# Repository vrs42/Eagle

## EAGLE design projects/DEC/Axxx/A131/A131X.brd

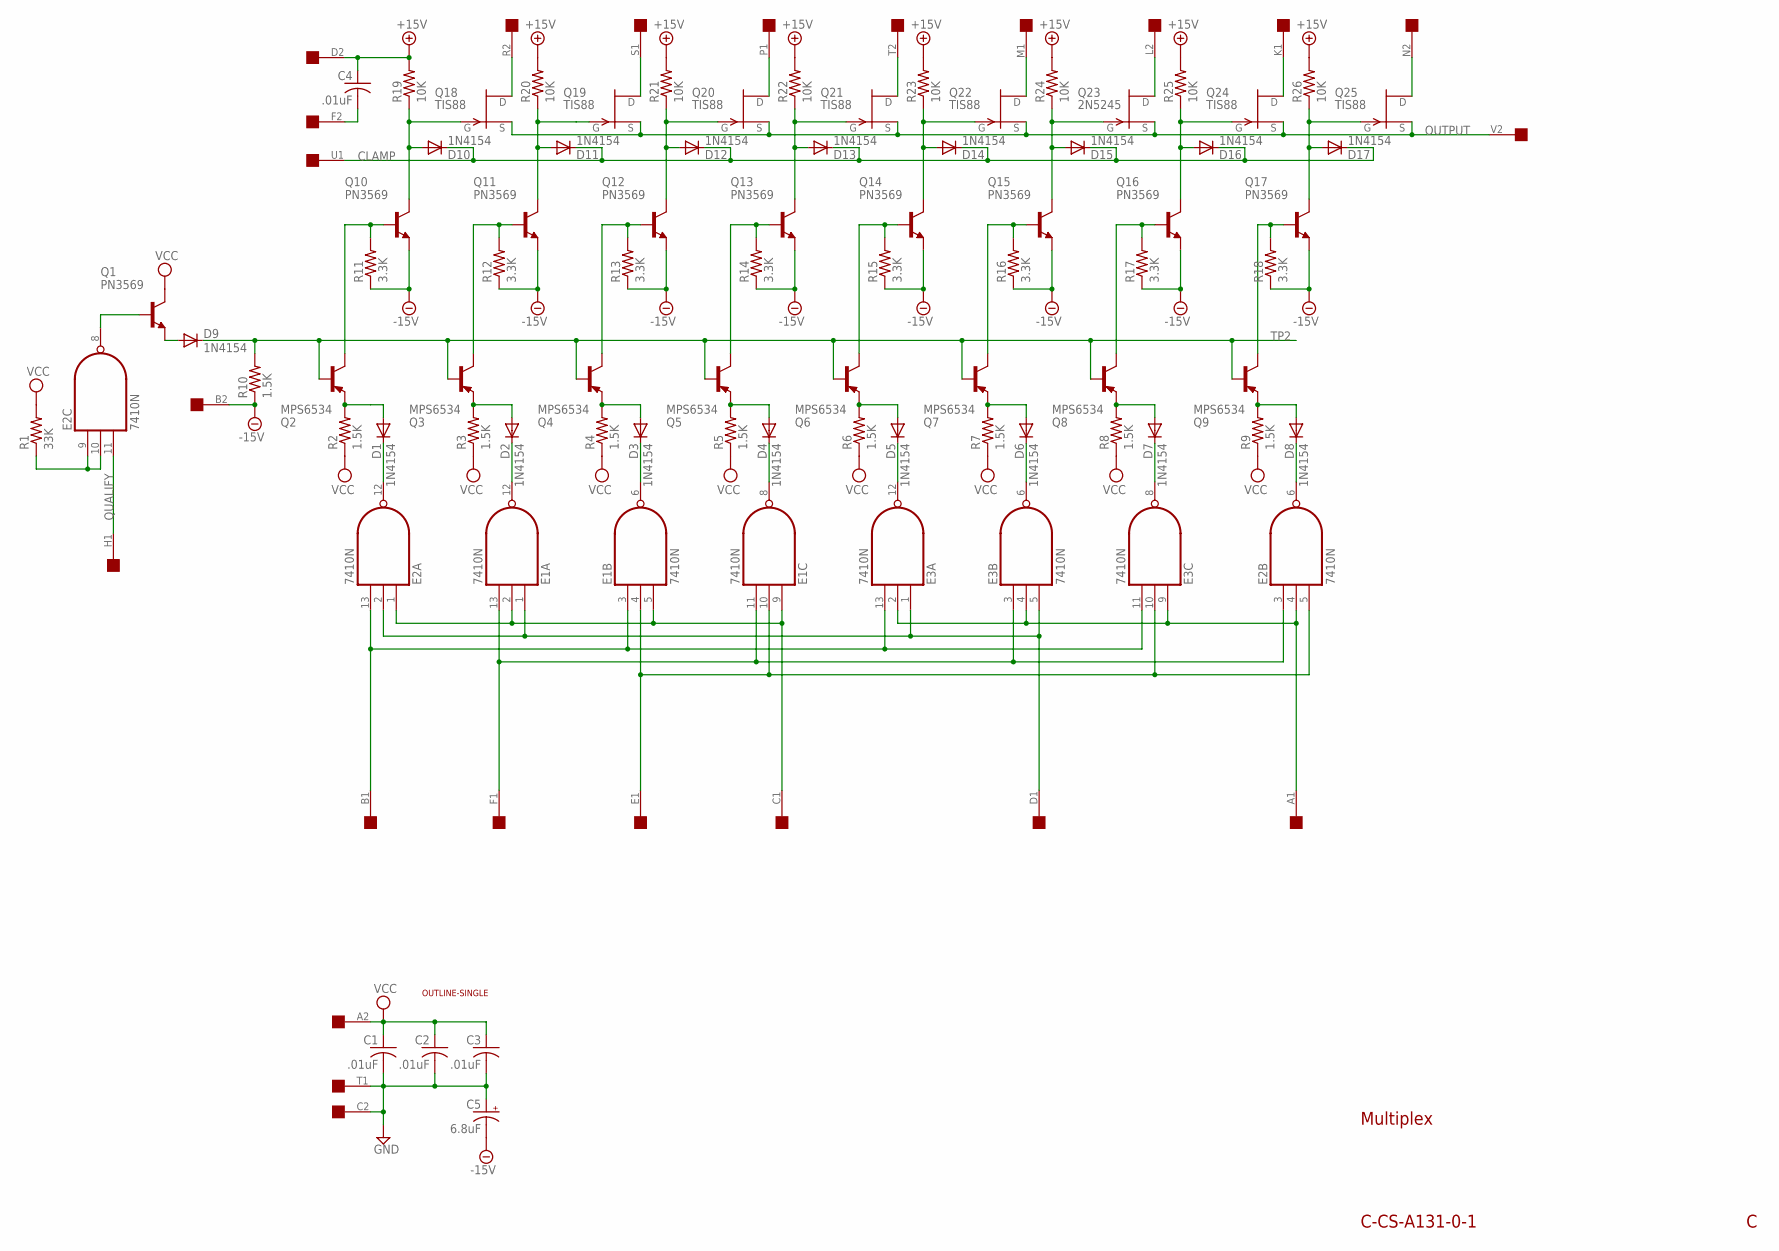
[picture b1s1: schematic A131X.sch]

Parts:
C1, C2, C3, C4: .01uF; C050-025X075
C5: 6.8uF; E12-8
D1, D2, D3, D4, D5, D6, D7, D8, D9, D10, D11, D12, D13, D14, D15, D16, D17: 1N4154; DO35-10
E1, E2, E3: 7410N; DIL14
Q1, Q10, Q11, Q12, Q13, Q14, Q15, Q16, Q17: PN3569; TO5
Q2, Q3, Q4, Q5, Q6, Q7, Q8, Q9: MPS6534; TO5
Q18, Q19, Q20, Q21, Q22, Q24, Q25: TIS88; TO39
Q23: 2N5245; TO39
R1: 33K; 0207/10
R2, R3, R4, R5, R6, R7, R8, R9, R10: 1.5K; 0207/10
R11, R12, R13, R14, R15, R16, R17, R18: 3.3K; 0207/10
R19, R20, R21, R22, R23, R24, R25, R26: 10K; 0207/10
U$1: OUTLINE-SINGLE; SINGLE
U$2: SINGLE; EDGE-CON2

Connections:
+15V: C4.1, R19.2, R20.2, R21.2, R22.2, R23.2, R24.2, R25.2, R26.2, U$2.D2
-15V: C5.-, Q10.1 (E), Q11.1 (E), Q12.1 (E), Q13.1 (E), Q14.1 (E), Q15.1 (E), Q16.1 (E), Q17.1 (E), R10.1, R11.1, R12.1, R13.1, R14.1, R15.1, R16.1, R17.1, R18.1, U$2.B2
CLAMP: D10.C, D11.C, D12.C, D13.C, D14.C, D15.C, D16.C, D17.C, U$2.U1
GND: C1.2, C2.2, C3.2, C5.+, E1.7 (GND), E2.7 (GND), E3.7 (GND), U$2.C2, U$2.T1
unnamed: E2.9 (I0), E2.10 (I1), R1.1
unnamed: D10.A, Q10.3 (C), Q18.3 (G), R19.1
unnamed: D12.A, Q12.3 (C), Q20.3 (G), R21.1
unnamed: D13.A, Q13.3 (C), Q21.3 (G), R22.1
unnamed: D14.A, Q14.3 (C), Q22.3 (G), R23.1
unnamed: D15.A, Q15.3 (C), Q23.3 (G), R24.1
unnamed: D16.A, Q16.3 (C), Q24.3 (G), R25.1
unnamed: D17.A, Q17.3 (C), Q25.3 (G), R26.1
unnamed: Q18.2 (D), U$2.R2
unnamed: Q19.2 (D), U$2.S1
unnamed: Q20.2 (D), U$2.P1
unnamed: Q21.2 (D), U$2.T2
unnamed: Q22.2 (D), U$2.M1
unnamed: Q23.2 (D), U$2.L2
unnamed: Q24.2 (D), U$2.K1
unnamed: Q25.2 (D), U$2.N2
unnamed: C4.2, U$2.F2
unnamed: Q2.3 (C), Q10.2 (B), R11.2
unnamed: Q3.3 (C), Q11.2 (B), R12.2
unnamed: Q4.3 (C), Q12.2 (B), R13.2
unnamed: Q5.3 (C), Q13.2 (B), R14.2
unnamed: Q6.3 (C), Q14.2 (B), R15.2
unnamed: Q9.3 (C), Q17.2 (B), R18.2
unnamed: Q8.3 (C), Q16.2 (B), R17.2
unnamed: Q7.3 (C), Q15.2 (B), R16.2
unnamed: D1.A, Q2.1 (E), R2.2
unnamed: D2.A, Q3.1 (E), R3.2
unnamed: D3.A, Q4.1 (E), R4.2
unnamed: D4.A, Q5.1 (E), R5.2
unnamed: D5.A, Q6.1 (E), R6.2
unnamed: D6.A, Q7.1 (E), R7.2
unnamed: D7.A, Q8.1 (E), R8.2
unnamed: D8.A, Q9.1 (E), R9.2
unnamed: E2.8 (O), Q1.2 (B)
unnamed: D9.A, Q1.1 (E)
unnamed: D1.C, E2.12 (O)
unnamed: D2.C, E1.12 (O)
unnamed: D3.C, E1.6 (O)
unnamed: D4.C, E1.8 (O)
unnamed: D5.C, E3.12 (O)
unnamed: D6.C, E3.6 (O)
unnamed: D7.C, E3.8 (O)
unnamed: D8.C, E2.6 (O)
unnamed: E1.3 (I0), E2.13 (I2), E3.11 (I2), E3.13 (I2), U$2.B1
unnamed: E1.11 (I2), E1.13 (I2), E2.3 (I0), E3.3 (I0), U$2.F1
unnamed: E1.4 (I1), E1.10 (I1), E2.5 (I2), E3.10 (I1), U$2.E1
unnamed: E1.2 (I1), E1.5 (I2), E1.9 (I0), E2.1 (I0), U$2.C1
unnamed: D11.A, Q11.3 (C), Q19.3 (G), R20.1
unnamed: E2.4 (I1), E3.2 (I1), E3.4 (I1), E3.9 (I0), U$2.A1
unnamed: E1.1 (I0), E2.2 (I1), E3.1 (I0), E3.5 (I2), U$2.D1
OUTPUT: Q18.1 (S), Q19.1 (S), Q20.1 (S), Q21.1 (S), Q22.1 (S), Q23.1 (S), Q24.1 (S), Q25.1 (S), U$2.V2
QUALIFY: E2.11 (I2), U$2.H1
TP2: D9.C, Q2.2 (B), Q3.2 (B), Q4.2 (B), Q5.2 (B), Q6.2 (B), Q7.2 (B), Q8.2 (B), Q9.2 (B), R10.2
VCC: C1.1, C2.1, C3.1, E1.14 (VCC), E2.14 (VCC), E3.14 (VCC), Q1.3 (C), R1.2, R2.1, R3.1, R4.1, R5.1, R6.1, R7.1, R8.1, R9.1, U$2.A2

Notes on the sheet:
C-CS-A131-0-1
Multiplex

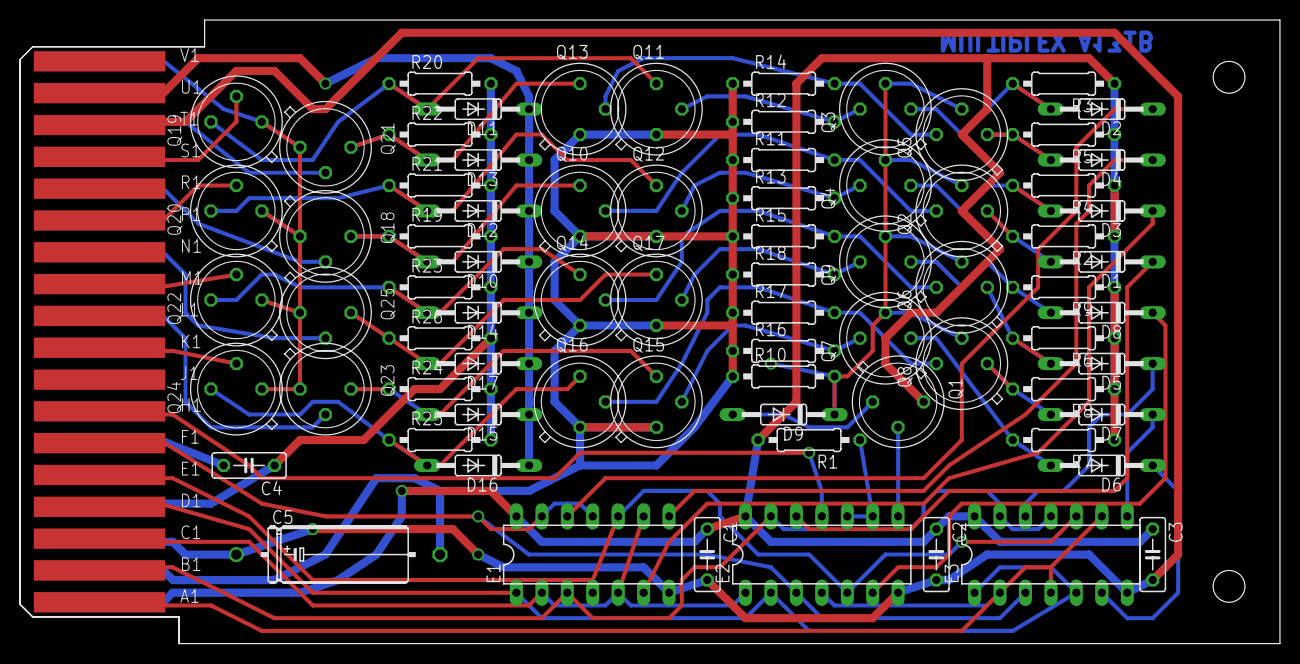
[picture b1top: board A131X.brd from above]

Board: 2 copper layers, 125.7 x 62.2 mm, 78 parts (0 on the bottom side), 58 nets.

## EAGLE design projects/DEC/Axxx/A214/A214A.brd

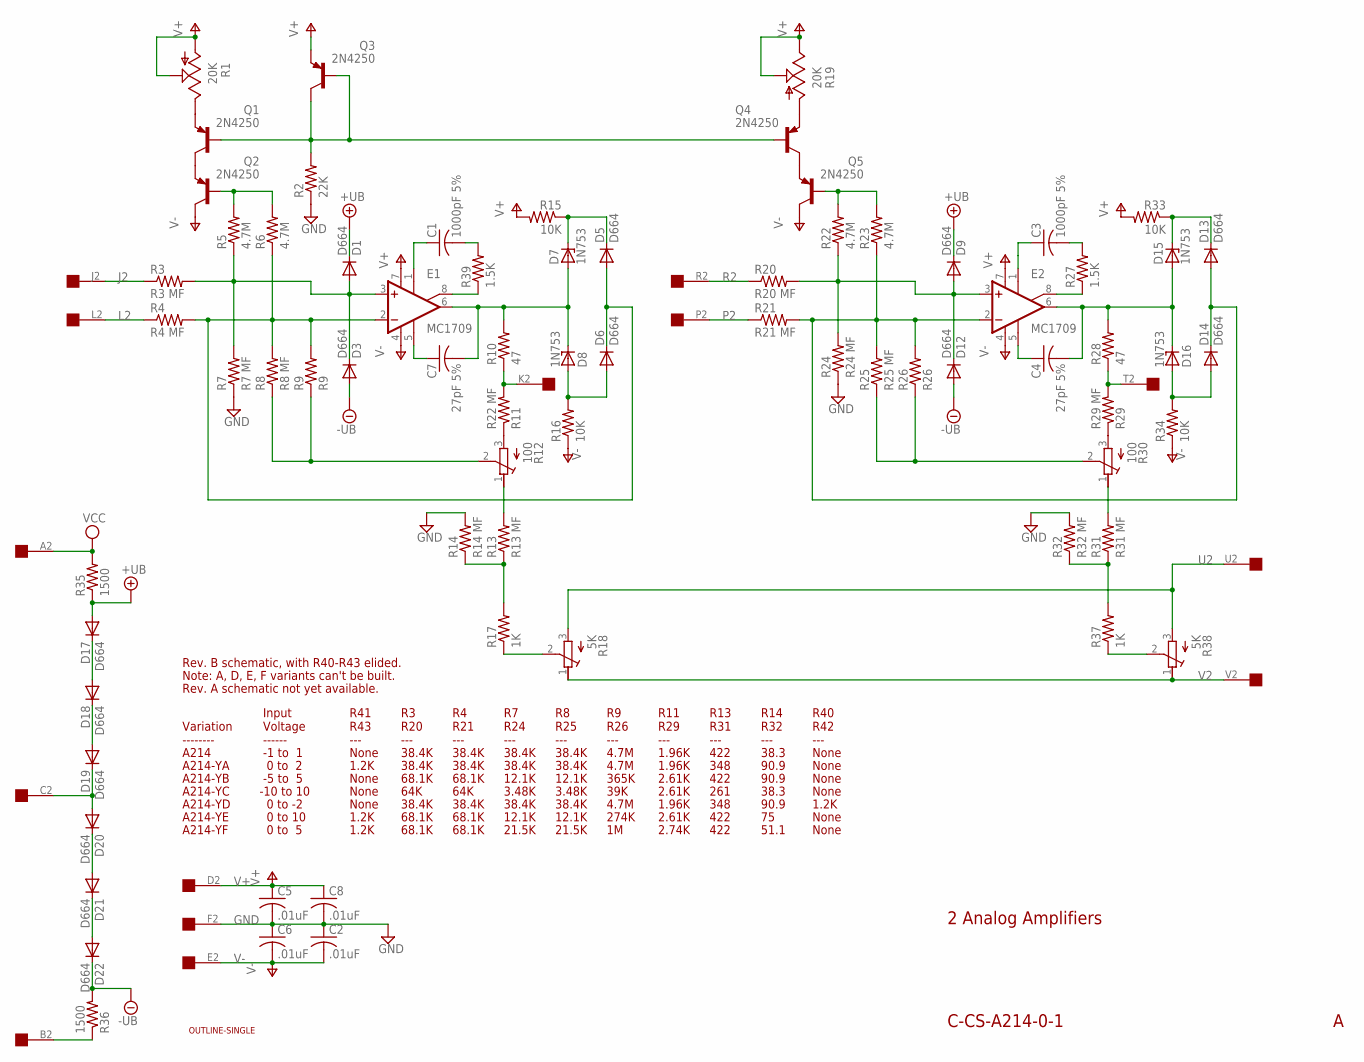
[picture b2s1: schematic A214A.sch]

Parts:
C1, C3: 1000pF 5%; C050-030X075
C2, C5, C6, C8: .01uF; C063-025X075
C4, C7: 27pF 5%; C063-025X075
D1, D3, D5, D6, D9, D12, D13, D14, D17, D18, D19, D20, D21, D22: D664; DO35-10
D7, D8, D15, D16: 1N753; DO41Z10
E1, E2: MC1709; H08C
Q1, Q2, Q3, Q4, Q5: 2N4250; TO5
R1, R19: 20K; B25P
R2: 22K; 0207/10
R3: R3 MF; 0207/15
R4: R4 MF; 0207/15
R5, R6, R22, R23: 4.7M; 0207/10
R7: R7 MF; 0207/15
R8: R8 MF; 0207/15
R9: R9; 0207/10
R10, R28: 47; 0207/10
R11: R22 MF; 0207/15
R12, R30: 100; 3006Y
R13: R13 MF; 0207/15
R14: R14 MF; 0207/15
R15, R16, R33, R34: 10K; 0207/10
R17, R37: 1K; 0207/10
R18, R38: 5K; 3006Y
R20: R20 MF; 0207/15
R21: R21 MF; 0207/15
R24: R24 MF; 0207/15
R25: R25 MF; 0207/15
R26: R26; 0207/10
R27, R39: 1.5K; 0207/10
R29: R29 MF; 0207/15
R31: R31 MF; 0207/15
R32: R32 MF; 0207/15
R35, R36: 1500; 0207/10
U$1: OUTLINE-SINGLE; SINGLE
U$2: EDGE-CON2

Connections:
+UB: D1.C, D9.C, D17.A, R35.1
-UB: D3.A, D12.A, D22.C, R36.2
B2: R36.1, U$2.B2
GND: C2.1, C5.2, C6.1, C8.2, R2.1, R7.1, R14.2, R24.1, R32.2, U$2.F2
J2: R3.1, U$2.J2
K2: R10.1, R11.2, U$2.K2
L2: R4.1, U$2.L2
unnamed: Q1.1 (E), R1.E
unnamed: Q1.3 (C), Q2.1 (E)
unnamed: Q2.2 (B), R5.2, R6.2
unnamed: Q1.2 (B), Q3.2 (B), Q3.3 (C), Q4.2 (B), R2.2
unnamed: D1.A, D3.C, E1.3 (+IN), R3.2, R5.1, R7.2
unnamed: D5.A, D6.C, E1.2 (-IN), R4.2, R6.1, R8.2, R9.2
unnamed: R8.1, R9.1, R12.2 (S)
unnamed: C1.1, E1.1 (ON1)
unnamed: D17.C, D18.A
unnamed: C1.2, R39.2
unnamed: D21.C, D22.A
unnamed: D20.C, D21.A
unnamed: D19.C, D20.A, U$2.C2
unnamed: D18.C, D19.A
unnamed: E1.8 (ON2), R39.1
unnamed: C7.1, E1.5 (OPT)
unnamed: C7.2, D7.A, D8.C, E1.6 (OUT), R10.2
unnamed: D6.A, D8.A, R16.2
unnamed: D5.C, D7.C, R15.1
unnamed: Q4.1 (E), R19.A
unnamed: R11.1, R12.3 (E)
unnamed: R12.1 (A), R13.2
unnamed: R13.1, R14.1, R17.2
unnamed: R17.1, R18.2 (S)
unnamed: C3.2, R27.2
unnamed: Q4.3 (C), Q5.1 (E)
unnamed: Q5.2 (B), R22.2, R23.2
unnamed: D9.A, D12.C, E2.3 (+IN), R20.2, R22.1, R24.2
unnamed: R25.1, R26.1, R30.2 (S)
unnamed: C3.1, E2.1 (ON1)
unnamed: C4.2, D15.A, D16.C, E2.6 (OUT), R28.2
unnamed: E2.8 (ON2), R27.1
unnamed: C4.1, E2.5 (OPT)
unnamed: D14.A, D16.A, R34.2
unnamed: D13.C, D15.C, R33.1
unnamed: D13.A, D14.C, E2.2 (-IN), R21.2, R23.1, R25.2, R26.2
unnamed: R29.1, R30.3 (E)
unnamed: R30.1 (A), R31.2
unnamed: R31.1, R32.1, R37.2
unnamed: R37.1, R38.2 (S)
P2: R21.1, U$2.P2
R2: R20.1, U$2.R2
T2: R28.1, R29.2, U$2.T2
U2: R18.3 (E), R38.3 (E), U$2.U2
V2: R18.1 (A), R38.1 (A), U$2.V2
V+: C5.1, C8.1, E1.7 (V+), E2.7 (V+), Q3.1 (E), R1.A, R1.S, R15.2, R19.E, R19.S, R33.2, U$2.D2
V-: C2.2, C6.2, E1.4 (V-), E2.4 (V-), Q2.3 (C), Q5.3 (C), R16.1, R34.1, U$2.E2
VCC: R35.2, U$2.A2

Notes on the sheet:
2 Analog Amplifiers
C-CS-A214-0-1
Input Voltage ------
0 to 10
-1 to 1
0 to 2
-10 to 10
0 to -2
0 to 5
R41 R43 ---
Variation --------
None
-5 to 5
1.2K
A214
A214-YA
A214-YB
A214-YC
A214-YD
A214-YE
A214-YF
R3 R20 ---
R4 R21 ---
R7 R24 ---
R8 R25 ---
R9 R26 ---
R11 R29 ---
R13 R31 ---
R14 R32 ---
R40 R42 ---
38.4K
68.1K
64K
3.48K
12.1K
21.5K
4.7M
365K
39K
274K

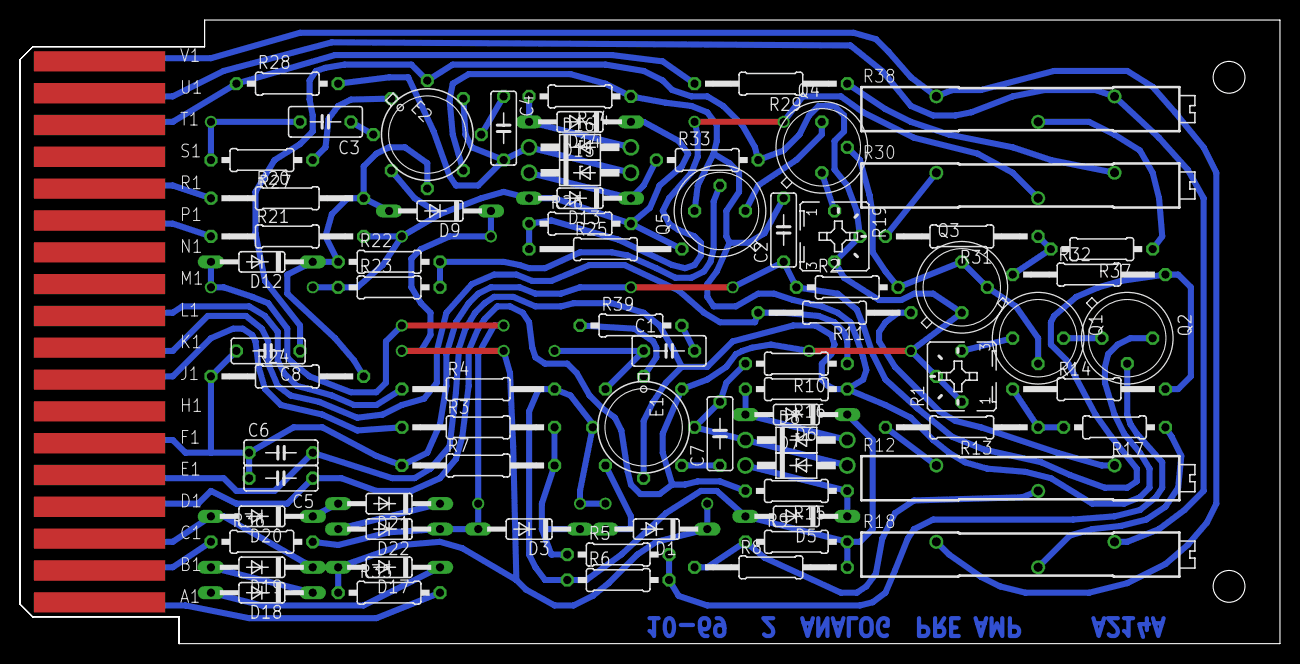
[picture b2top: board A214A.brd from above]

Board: 2 copper layers, 125.7 x 62.2 mm, 74 parts (0 on the bottom side), 55 nets.

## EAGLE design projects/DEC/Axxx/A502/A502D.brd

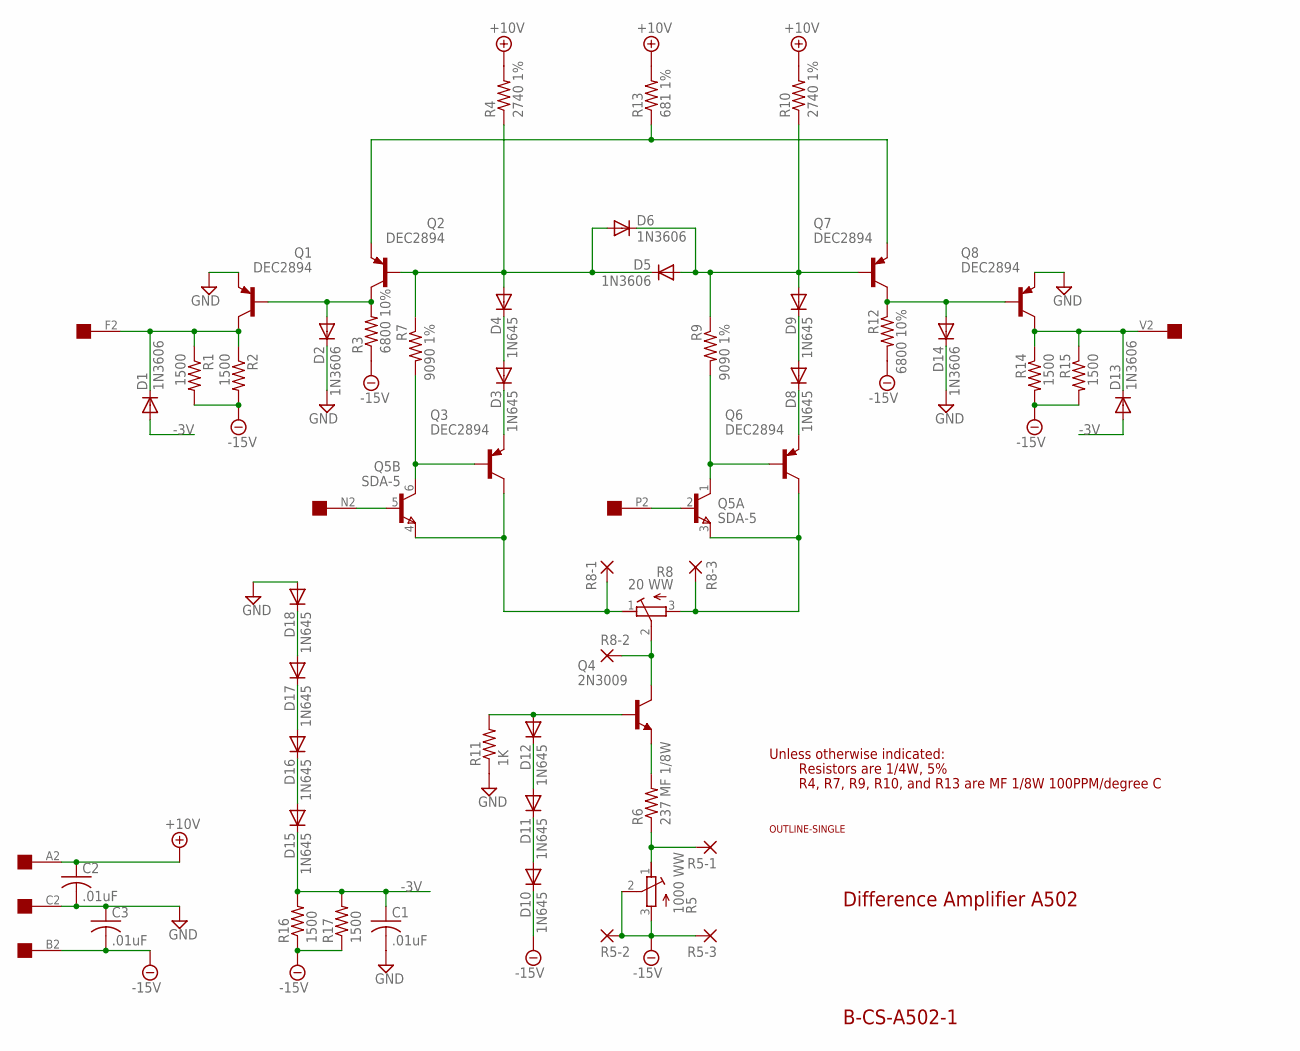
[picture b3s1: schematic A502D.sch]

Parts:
C1, C2, C3: .01uF; C050-025X075
D1, D2, D5, D6, D13, D14: 1N3606; DO35-10
D3, D4, D8, D9, D10, D11, D12, D15, D16, D17, D18: 1N645; DO35-10
Q1, Q2, Q3, Q6, Q7, Q8: DEC2894; TO39
Q4: 2N3009; TO5
Q5: SDA-5; TO78
R1, R2, R14, R15, R16, R17: 1500; 0207/10
R3, R12: 6800 10%; 0207/10
R4, R10: 2740 1%; 0207/15
R5: 1000 WW; 3006Y
R5-1, R5-2, R5-3, R8-1, R8-2, R8-3: 2,54/0,8
R6: 237 MF 1/8W; 0207/15
R7, R9: 9090 1%; 0207/15
R8: 20 WW; 3006Y
R11: 1K; 0207/10
R13: 681 1%; 0207/15
U$2: OUTLINE-SINGLE; SINGLE
U$3: EDGE-1; EDGE-CON1

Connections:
+10V: C2.1, R4.2, R10.2, R13.2, U$3.A2
-3V: C1.1, D1.A, D13.A, D15.C, R16.2, R17.2
-15V: C3.2, D10.C, R1.2, R2.2, R3.1, R5.2 (S), R5.3 (E), R5-2.1, R5-3.1, R12.2, R14.2, R15.2, R16.1, R17.1, U$3.B2
GND: C1.2, C2.2, C3.1, D2.C, D14.C, D18.A, Q1.1 (E), Q8.1 (E), R11.1, U$3.C2
unnamed: Q5.2 (B), U$3.P2
unnamed: Q5.5 (B), U$3.N2
unnamed: Q5.3 (E), Q6.3 (C), R8.3 (E), R8-3.1
unnamed: Q5.1 (C), Q6.2 (B), R9.2
unnamed: Q3.3 (C), Q5.4 (E), R8.1 (A), R8-1.1
unnamed: Q3.2 (B), Q5.6 (C), R7.2
unnamed: D12.A, Q4.2 (B), R11.2
unnamed: D17.A, D18.C
unnamed: Q4.3 (C), R8.2 (S), R8-2.1
unnamed: R5.1 (A), R5-1.1, R6.1
unnamed: D16.A, D17.C
unnamed: D15.A, D16.C
unnamed: D1.C, Q1.3 (C), R1.1, R2.1, U$3.F2
unnamed: D10.A, D11.C
unnamed: D2.A, Q1.2 (B), Q2.3 (C), R3.2
unnamed: D5.A, D6.C, D9.A, Q7.2 (B), R9.1, R10.1
unnamed: D11.A, D12.C
unnamed: D14.A, Q7.3 (C), Q8.2 (B), R12.1
unnamed: D13.C, Q8.3 (C), R14.1, R15.1, U$3.V2
unnamed: D4.A, D5.C, D6.A, Q2.2 (B), R4.1, R7.1
unnamed: Q2.1 (E), Q7.1 (E), R13.1
unnamed: D3.A, D4.C
unnamed: Q4.1 (E), R6.2
unnamed: D8.A, D9.C
unnamed: D3.C, Q3.1 (E)
unnamed: D8.C, Q6.1 (E)

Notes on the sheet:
Difference Amplifier A502
B-CS-A502-1
Unless otherwise indicated:
Resistors are 1/4W, 5%
R4, R7, R9, R10, and R13 are MF 1/8W 100PPM/degree C

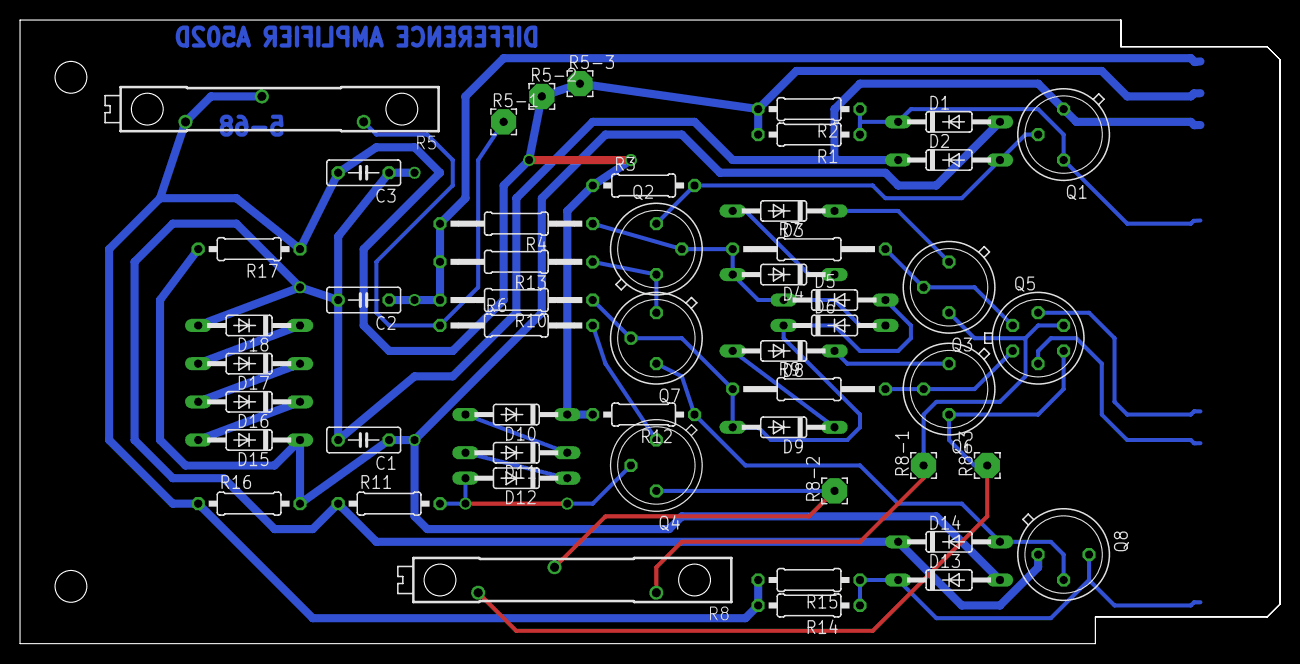
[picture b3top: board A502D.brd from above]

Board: 2 copper layers, 125.7 x 62.2 mm, 53 parts (0 on the bottom side), 30 nets.

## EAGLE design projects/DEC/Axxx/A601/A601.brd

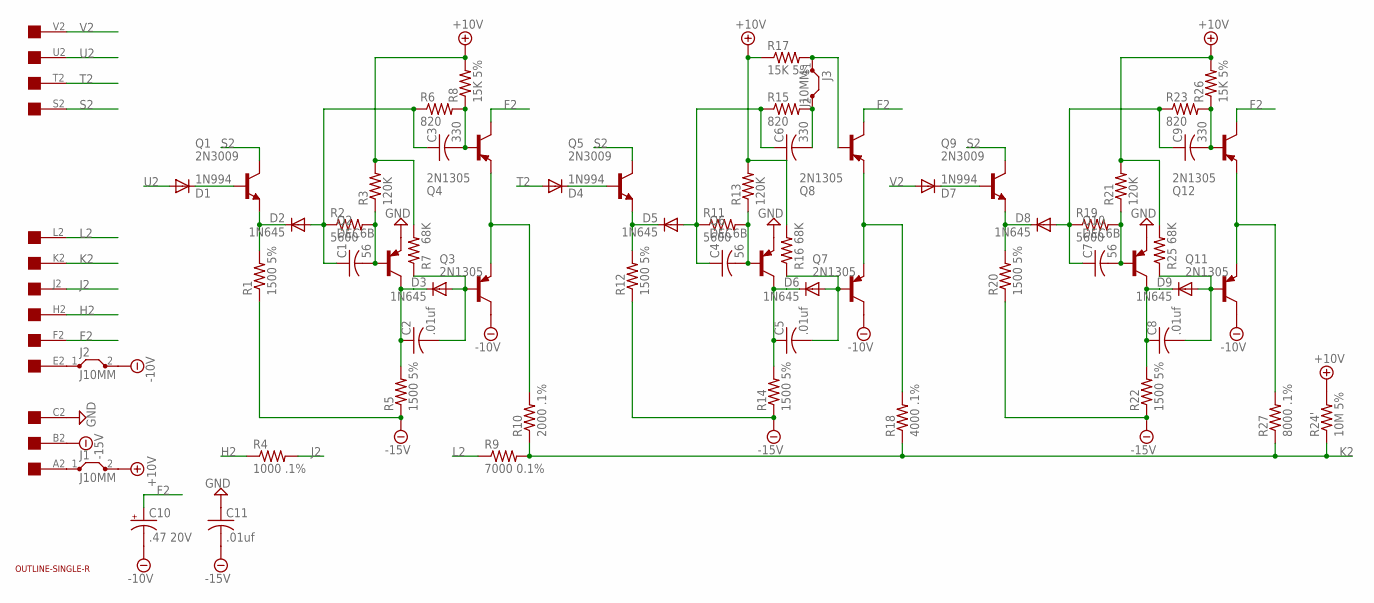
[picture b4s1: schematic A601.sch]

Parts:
C1, C4, C7: 56; C075-032X103
C2, C5, C8, C11: .01uf; C050-025X075
C3, C6, C9: 330; C102-043X133
C10: .47 20V; E22-6
D1, D4, D7: 1N994; DO35-10
D2, D3, D5, D6, D8, D9: 1N645; DO35-10
J1, J2, J3: J10MM; 10
Q1, Q5, Q9: 2N3009; TO39
Q2, Q6, Q10: DEC6B; TO39
Q3, Q4, Q7, Q8, Q11, Q12: 2N1305; TO39
R1, R5, R12, R14, R20, R22: 1500 5%; 0207/10
R2, R11, R19: 5600; 0207/10
R3, R13, R21: 120K; 0207/10
R4: 1000 .1%; 0309/12
R6, R15, R23: 820; 0207/10
R7, R16, R25: 68K; 0207/10
R8, R17, R26: 15K 5%; 0207/10
R9: 7000 0.1%; 0309/12
R10: 2000 .1%; 0309/12
R18: 4000 .1%; 0309/12
R24': 10M 5%; 0207/10
R27: 8000 .1%; 0309/12
U$2: OUTLINE-SINGLE-R; SINGLE-R
U$3: EDGE-1; EDGE-CON1

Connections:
+10V: J1.2, R3.2, R7.2, R8.2, R13.2, R16.2, R17.1, R21.2, R24'.2, R25.2, R26.2
-10V: C10.-, J2.2, Q3.3 (C), Q7.3 (C), Q11.3 (C)
-15V: C11.2, R1.1, R5.1, R12.1, R14.1, R20.1, R22.1, U$3.B2
F2: C10.+, Q4.3 (C), Q8.3 (C), Q12.3 (C), U$3.F2
GND: C11.1, Q2.1 (E), Q6.1 (E), Q10.1 (E), U$3.C2
H2: R4.1, U$3.H2
J2: R4.2, U$3.J2
K2: R9.2, R10.1, R18.1, R24'.1, R27.1, U$3.K2
L2: R9.1, U$3.L2
unnamed: D1.C, Q1.2 (B)
unnamed: D2.C, Q1.1 (E), R1.2
unnamed: C1.1, C3.1, D2.A, R2.1, R6.1
unnamed: C1.2, Q2.2 (B), R2.2, R3.1
unnamed: C3.2, Q4.2 (B), R6.2, R8.1
unnamed: C2.1, D3.C, Q2.3 (C), R5.2
unnamed: C2.2, D3.A, Q3.2 (B), R7.1
unnamed: Q3.1 (E), Q4.1 (E), R10.2
unnamed: J2.1, U$3.E2
unnamed: D4.C, Q5.2 (B)
unnamed: D5.C, Q5.1 (E), R12.2
unnamed: C4.1, C6.1, D5.A, R11.1, R15.1
unnamed: C4.2, Q6.2 (B), R11.2, R13.1
unnamed: C6.2, J3.2, R15.2
unnamed: C5.1, D6.C, Q6.3 (C), R14.2
unnamed: C5.2, D6.A, Q7.2 (B), R16.1
unnamed: Q7.1 (E), Q8.1 (E), R18.2
unnamed: D7.C, Q9.2 (B)
unnamed: D8.C, Q9.1 (E), R20.2
unnamed: C7.1, C9.1, D8.A, R19.1, R23.1
unnamed: C7.2, Q10.2 (B), R19.2, R21.1
unnamed: C9.2, Q12.2 (B), R23.2, R26.1
unnamed: C8.1, D9.C, Q10.3 (C), R22.2
unnamed: C8.2, D9.A, Q11.2 (B), R25.1
unnamed: Q11.1 (E), Q12.1 (E), R27.2
unnamed: J1.1, U$3.A2
unnamed: J3.1, Q8.2 (B), R17.2
S2: Q1.3 (C), Q5.3 (C), Q9.3 (C), U$3.S2
T2: D4.A, U$3.T2
U2: D1.A, U$3.U2
V2: D7.A, U$3.V2

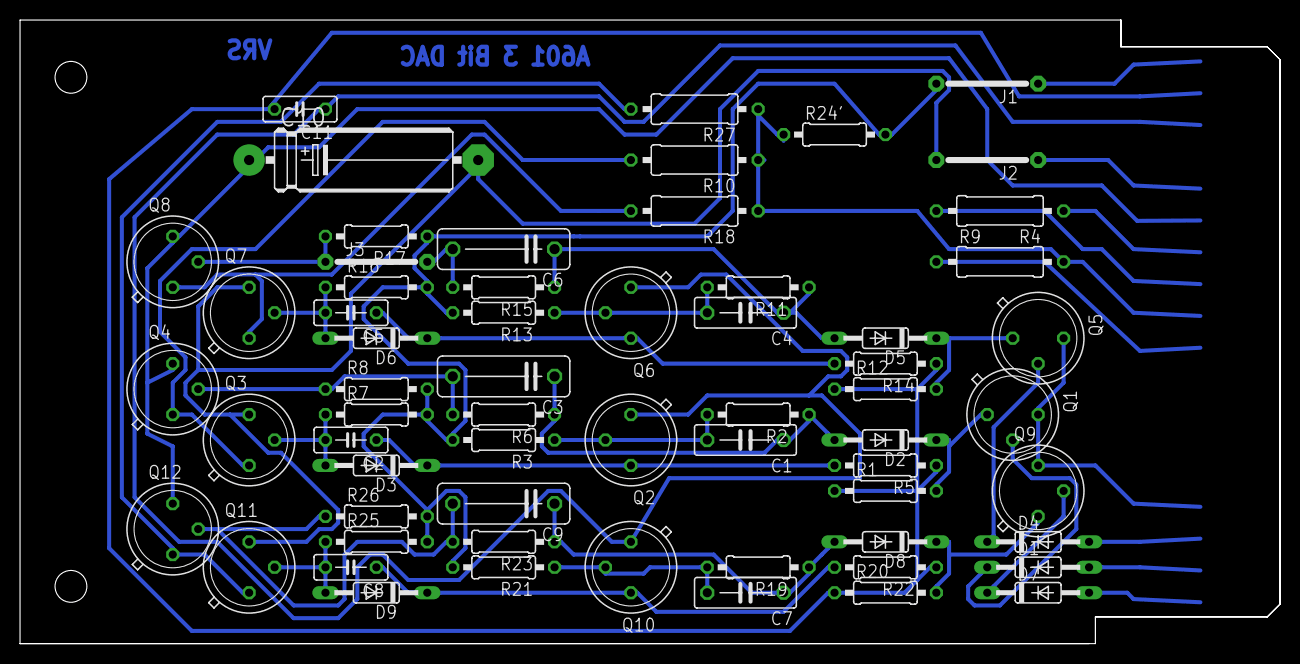
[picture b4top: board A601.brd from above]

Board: 2 copper layers, 125.7 x 62.2 mm, 64 parts (0 on the bottom side), 40 nets.
